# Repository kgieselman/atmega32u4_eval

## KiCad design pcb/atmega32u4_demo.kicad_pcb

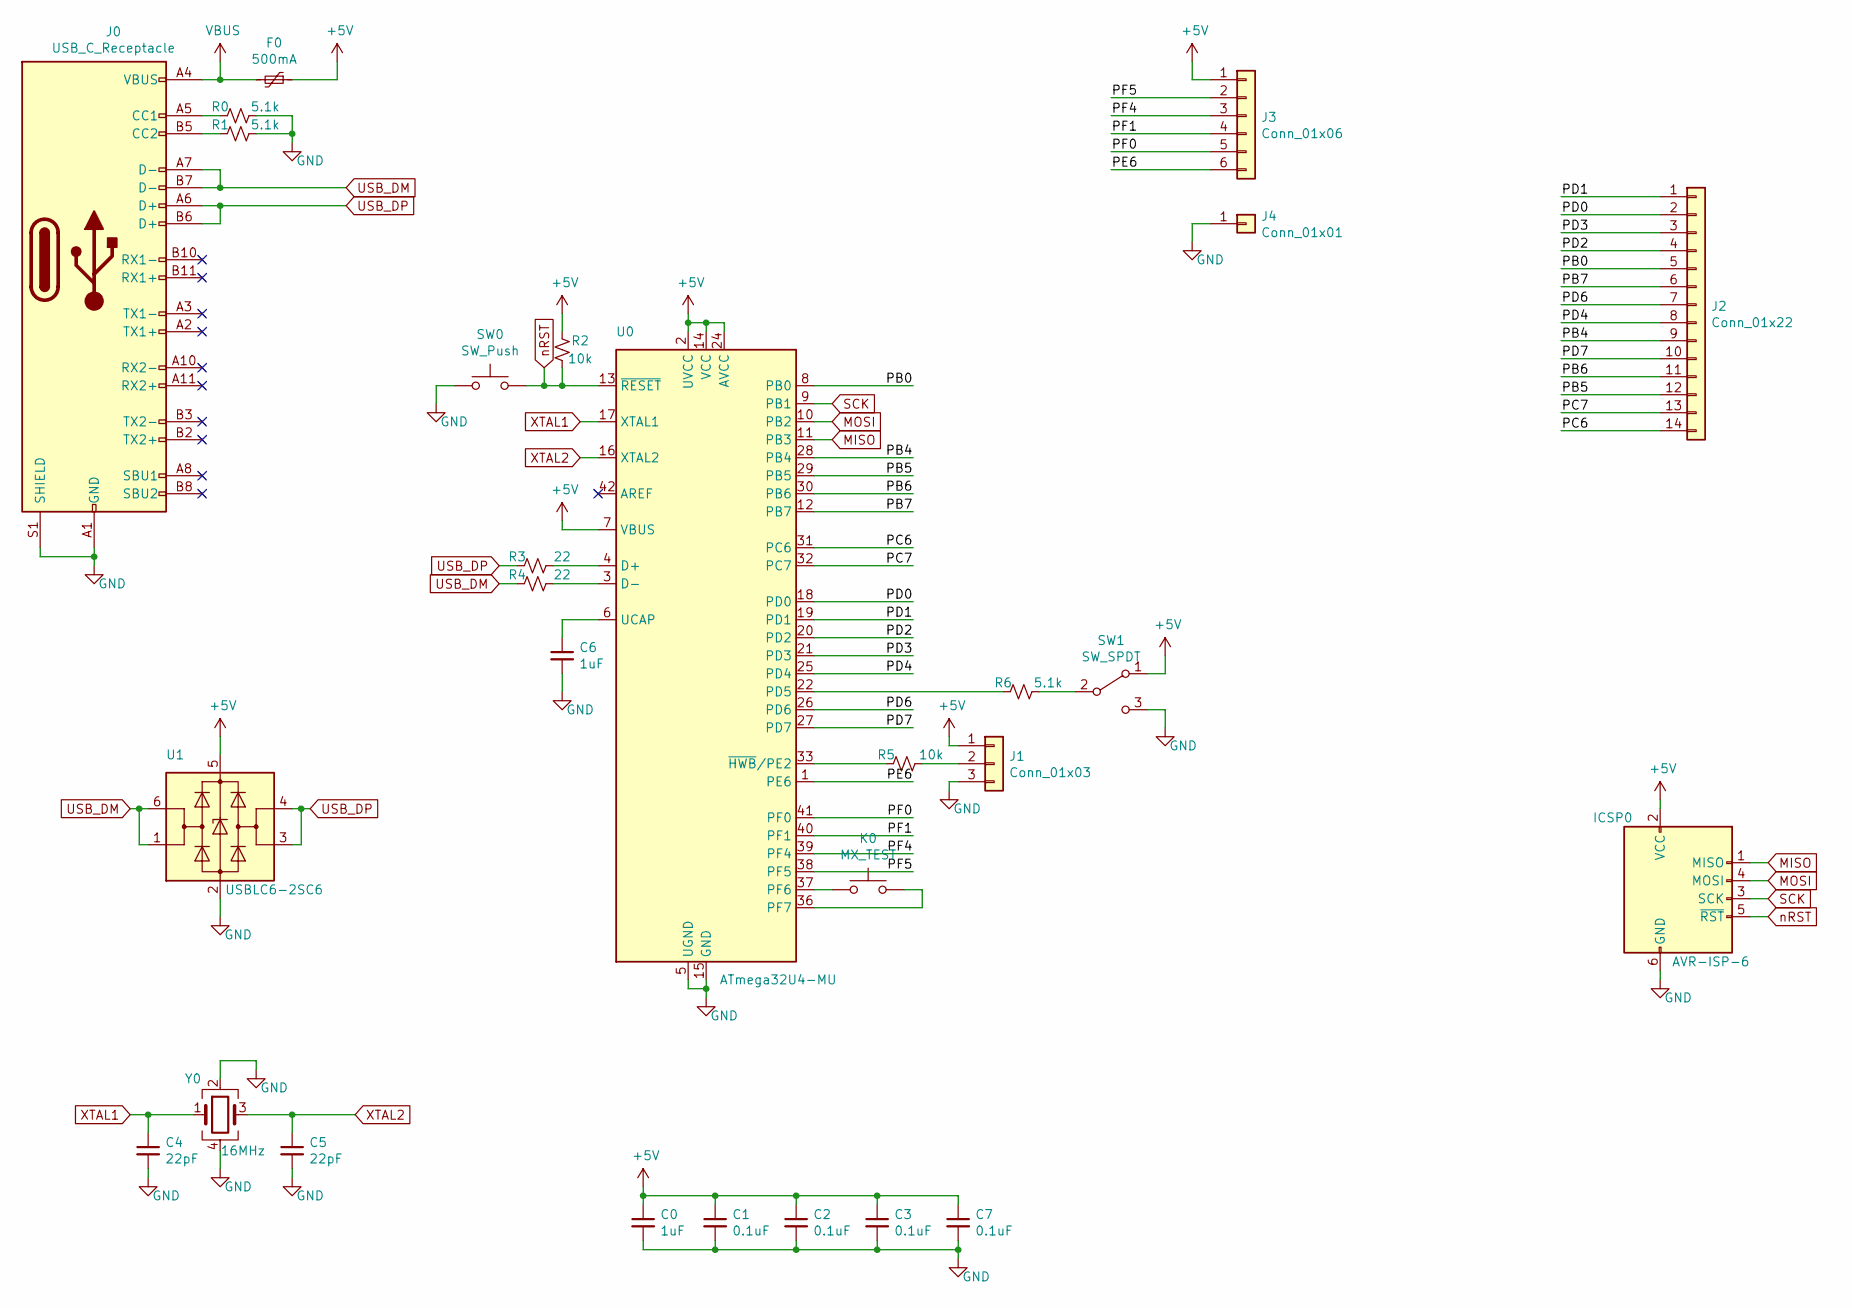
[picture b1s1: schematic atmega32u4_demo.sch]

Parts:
C0, C6: 1uF; C_0603_1608Metric; LCSC C15849
C1, C2, C3, C7: 0.1uF; C_0603_1608Metric; LCSC C14663
C4, C5: 22pF; C_0603_1608Metric; LCSC C1653
F0: 500mA; Fuse_1206_3216Metric; LCSC C369159
ICSP0: AVR-ISP-6; Tag-Connect_TC2030-IDC-NL_2x03_P1.27mm_Vertical; LCSC DNI
J0: USB_C_Receptacle; USB_C_Receptacle_HRO_TYPE-C-31-M-12; LCSC C165948
J1: Conn_01x03; PinSocket_1x03_P2.54mm_Vertical; LCSC DNI
J2: Conn_01x22; PinSocket_2x07_P2.54mm_Vertical; LCSC DNI
J3: Conn_01x06; PinSocket_1x06_P2.54mm_Vertical; LCSC DNI
J4: Conn_01x01; PinSocket_1x01_P2.54mm_Vertical; LCSC DNI
K0: MX_TEST; MX_hotswap_1U; LCSC DNI
R0, R1, R6: 5.1k; R_0603_1608Metric; LCSC C23186
R2, R5: 10k; R_0603_1608Metric; LCSC C25804
R3, R4: 22; R_0603_1608Metric; LCSC C23345
SW0: SW_Push; SPST_TS-1088-AR02016; LCSC C720477
SW1: SW_SPDT; slider; LCSC C189615
U0: ATmega32U4-MU; QFN-44-1EP_7x7mm_P0.5mm_EP5.2x5.2mm; LCSC C45874
U1: USBLC6-2SC6; SOT-23-6; LCSC C7519
Y0: 16MHz; Crystal_SMD_3225-4Pin_3.2x2.5mm; LCSC C179641

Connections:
+5V: C0.1, C1.1, C2.1, C3.1, C7.1, F0.1, ICSP0.2 (VCC), J1.1, J3.1, R2.1, SW1.1 (A), U0.2 (UVCC), U0.7 (VBUS), U0.14 (VCC), U0.24 (AVCC), U0.34 (VCC), U0.44 (AVCC), U1.5 (VBUS)
/PB0: J2.5, U0.8 (PB0)
/PB4: J2.9, U0.28 (PB4)
/PB5: J2.12, U0.29 (PB5)
/PB6: J2.11, U0.30 (PB6)
/PB7: J2.6, U0.12 (PB7)
/PC6: J2.14, U0.31 (PC6)
/PC7: J2.13, U0.32 (PC7)
/PD0: J2.2, U0.18 (PD0)
/PD1: J2.1, U0.19 (PD1)
/PD2: J2.4, U0.20 (PD2)
/PD3: J2.3, U0.21 (PD3)
/PD4: J2.8, U0.25 (PD4)
/PD6: J2.7, U0.26 (PD6)
/PD7: J2.10, U0.27 (PD7)
/PE6: J3.6, U0.1 (PE6)
/PF0: J3.5, U0.41 (PF0)
/PF1: J3.4, U0.40 (PF1)
/PF4: J3.3, U0.39 (PF4)
/PF5: J3.2, U0.38 (PF5)
GND: C0.2, C1.2, C2.2, C3.2, C4.2, C5.2, C6.2, C7.2, ICSP0.6 (GND), J0.A1 (GND), J0.A12 (GND), J0.B1 (GND), J0.B12 (GND), J0.S1 (SHIELD), J1.3, J4.1, R0.1, R1.1, SW0.1, SW1.3 (C), U0.5 (UGND), U0.15 (GND), U0.23 (GND), U0.35 (GND), U0.43 (GND), U0.45 (GND), U1.2 (GND), Y0.2, Y0.4
MISO: ICSP0.1 (MISO), U0.11 (PB3)
MOSI: ICSP0.4 (MOSI), U0.10 (PB2)
unnamed: C6.1, U0.6 (UCAP)
unnamed: J0.A5 (CC1), R0.2
unnamed: J0.B5 (CC2), R1.2
unnamed: J1.2, R5.1
unnamed: K0.1, U0.37 (PF6)
unnamed: K0.2, U0.36 (PF7)
unnamed: R3.1, U0.4 (D+)
unnamed: R4.1, U0.3 (D-)
unnamed: R5.2, U0.33 (~HWB~/PE2)
unnamed: R6.1, SW1.2 (B)
unnamed: R6.2, U0.22 (PD5)
SCK: ICSP0.3 (SCK), U0.9 (PB1)
USB_DM: J0.A7 (D-), J0.B7 (D-), R4.2, U1.1 (I/O1), U1.6 (I/O1)
USB_DP: J0.A6 (D+), J0.B6 (D+), R3.2, U1.3 (I/O2), U1.4 (I/O2)
VBUS: F0.2, J0.A4 (VBUS), J0.A9 (VBUS), J0.B4 (VBUS), J0.B9 (VBUS)
XTAL1: C4.1, U0.17 (XTAL1), Y0.1
XTAL2: C5.1, U0.16 (XTAL2), Y0.3
nRST: ICSP0.5 (~RST), R2.2, SW0.2, U0.13 (~RESET)

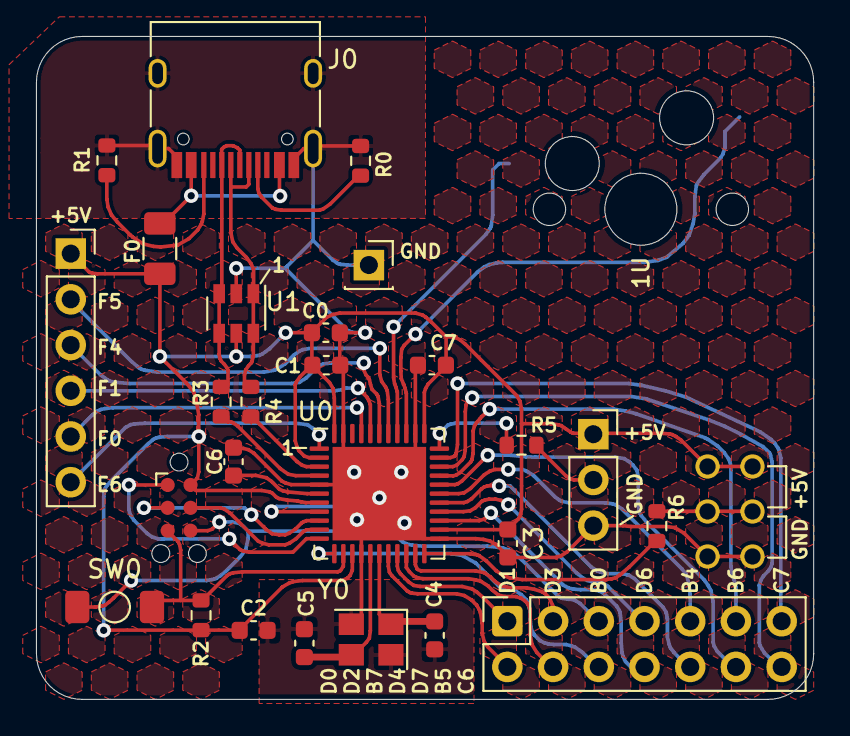
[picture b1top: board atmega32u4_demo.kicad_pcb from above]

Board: 2 copper layers, 43.2 x 36.8 mm, 28 parts (0 on the bottom side), 41 nets.

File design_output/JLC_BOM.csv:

Comment,Designator,Foorprint,LCSC Part #
1uF,C0 C6,0603,C15849
100nF,C1 C2 C3 C7,0603,C14663
22pF,C4 C5,0603,C1653
500mA,F0,1206,C369159
USB C,J0,HRO_TYPE-C-31-M-12,C165948
5.1k,R0 R1 R6,0603,C23186
22,R3 R4,0603,C23345
10k,R2 R5,0603,C25804
SPST,SW0,ts_1088,C720477
SPDT,SW1,custom,C189615
atmega32u4-mu,U0,QFN-44_7x7mm_P0.5mm,C45874
usblc6-2sc6,U1,SOT-23-6,C7519
16MHz,Y0,3225-4pin,C179641
